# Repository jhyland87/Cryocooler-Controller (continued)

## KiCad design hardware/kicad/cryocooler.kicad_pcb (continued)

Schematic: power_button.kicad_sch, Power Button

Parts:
C24: 100nF; C_0402_1005Metric
C41: 1uF; C_0603_1608Metric
C80: 47nF; C_0603_1608Metric
C84: 470nF; C_0805_2012Metric
D7: STATUS G=on R=standby; LED_Kingbright_APGB0607
D17: BZT52C15; D_SOD-123
Q1: AONR21307; AOS_DFN3x3A_8L_EP1
Q41: BSS138; SOT-23
R7, R8, R20: 10k; R_0402_1005Metric
R27: 100k; R_0402_1005Metric
R56: 220k; R_0402_1005Metric
R59: 82k; R_0402_1005Metric
R93: 13k; R_0402_1005Metric
R401: 2.2k; R_0402_1005Metric
SW3: POWER; SW_TE_1571300-2
U11: LTC2954CDDB-2; DFN-8-1EP_2x3mm_P0.5mm_EP0.61x2.2mm
U12: LM4040DBZ-5; SOT-23
U34: TPD1E05U06DPYR; Texas_DPY0002A_0.6x1mm_P0.65mm

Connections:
+3V3: Q41.1 (G), R8.2; also elsewhere on the board
+5V: R401.1; also elsewhere on the board
/Power Button/PWR_BTN: SW3.1, U11.3 (PB), U34.1 (IO)
/Power Button/STATUS_GA: D7.1 (GA), R401.2
/Power Button/STATUS_RA: D7.4 (RA), Q41.3 (D), R93.2
GND: C24.2, C41.2, D7.2 (GK), D7.3 (RK), Q41.2 (S), SW3.2, U11.1 (GND), U11.9 (EP), U12.2 (A), U34.2 (GND); also elsewhere on the board
unnamed: C80.1, C84.2, D17.2 (A), Q1.4 (G), R20.2, R27.2
unnamed: C41.1, U11.6 (PDT)
unnamed: R20.1, U11.7 (~EN)
unnamed: R7.1, R56.2, U11.5 (~KILL)
unnamed: R56.1, R59.2, U12.1 (K)
PWR_INT: R8.1, U11.8 (~INT); also elsewhere on the board
PWR_KILL: R7.2; also elsewhere on the board
VIN: C24.1, C84.1, D17.1 (K), Q1.1 (S), Q1.2 (S), Q1.3 (S), R27.1, R59.1, R93.1, U11.4 (VIN); also elsewhere on the board
VSW: C80.2, Q1.5 (D), Q1.6 (D), Q1.7 (D), Q1.8 (D); also elsewhere on the board

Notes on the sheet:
Q1 gate: 10k series and 47 nF to the drain limit the ramp to about 20 V/ms; 470 nF to the source holds Vgs under 1.1 V on a hot plug (10 x Cgd); the Zener caps Vgs at 15 V for input transients up to the 26 V TVS clamp.
STATUS LED: red = standby (about 0.8 mA from VIN, off when +3V3 is up), green = on (+5V, about 1 mA), both = +3V3 missing
LTC2954 DECOUPLING CAPACITORS
LTC2954-2: tap PB = on, hold = off. EN# drives the P-FET gate; KILL# from GPIO10 (active low, 100 ms pulse). INT# tells GPIO1 to shut down cleanly; holding PB cuts power about 6.4 s later (1 uF on PDT).

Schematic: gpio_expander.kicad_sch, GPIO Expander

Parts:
C35: 100nF; C_0402_1005Metric
U25: MCP23S08-E/ML; QFN-20-1EP_4x4mm_P0.5mm_EP2.7x2.7mm

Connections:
+3V3: C35.1, U25.4 (~RESET), U25.18 (VDD); also elsewhere on the board
DISP_BL_EN: U25.13 (GP4); also elsewhere on the board
EXPANDER_CS: U25.5 (~CS); also elsewhere on the board
GND: C35.2, U25.2 (A1), U25.3 (A0), U25.17 (VSS), U25.21 (EP); also elsewhere on the board
INA239_ALERT: U25.15 (GP6); also elsewhere on the board
PGN_15V: U25.10 (GP1); also elsewhere on the board
PGP_15V: U25.9 (GP0); also elsewhere on the board
SPI_MISO: U25.1 (SO); also elsewhere on the board
SPI_MOSI: U25.20 (SI); also elsewhere on the board
SPI_SCK: U25.19 (SCK); also elsewhere on the board
TOUCH_IRQ: U25.16 (GP7); also elsewhere on the board

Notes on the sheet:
All pins power up as inputs. RESET, A1 and A0 must be biased (datasheet Table 1-1). Exposed pad to VSS, in addition to pin 17. GP2, GP3 and GP5 are spare; firmware enables weak pull-ups on them. TSC2046 PENIRQ drives GP7.
MCP23S08 DECOUPLING CAPACITOR
MCP23S08: SPI mode 0 slave on the main bus (CS from the decoder). SO releases within 100 ns of CS rising (datasheet Fig. 2-6, parameter 14), so it shares SPI_MISO without a buffer. A1/A0 low: opcodes 0x40 / 0x41.

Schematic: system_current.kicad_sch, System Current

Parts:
C32: 100nF; C_0402_1005Metric
C46: 1uF; C_0603_1608Metric
C66: 100uF/25V; CP_Elec_8x10
C68: 100nF; C_0805_2012Metric
C83: 470nF; C_0805_2012Metric
D6: ALERT (red); LED_Kingbright_APGB0607
R9: 10k; R_0402_1005Metric
R78: 15m; R_2512_6332Metric
R79, R80: 49.9; R_0402_1005Metric
R81: 1.5k; R_0402_1005Metric
U23: INA239AIDGSR; TSSOP-10_3x3mm_P0.5mm

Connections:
+3V3: C32.1, C46.1, R9.2, R81.1, U23.6 (VS); also elsewhere on the board
+12V: C66.1, C68.1, R78.2, R79.1; also elsewhere on the board
/System Current/ALERT_LED_A: D6.4 (RA), R81.2
GND: C32.2, C46.2, C66.2, C68.2, U23.7 (GND); also elsewhere on the board
INA239_ALERT: D6.3 (RK), R9.1, U23.3 (~ALERT); also elsewhere on the board
INA239_CS: U23.1 (~CS); also elsewhere on the board
unnamed: C83.2, R80.2, U23.10 (IN+)
unnamed: C83.1, R79.2, U23.8 (VBUS), U23.9 (IN-)
SPI_MISO: U23.4 (SDO); also elsewhere on the board
SPI_MOSI: U23.2 (SDI); also elsewhere on the board
SPI_SCK: U23.5 (SCLK); also elsewhere on the board
VSW: R78.1, R80.1; also elsewhere on the board

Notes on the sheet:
INA239 DECOUPLING CAPACITORS
INA239 monitors the switched 12 V rail: 15 mOhm shunt, SPI mode 1 on the main bus (CS from the decoder), +/-163.84 mV range (~10.9 A). ALERT drives its LED and MCP23S08 GP6.

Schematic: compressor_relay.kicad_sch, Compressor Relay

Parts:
D3: COMP_RELAY G=on R=off; LED_Kingbright_APGB0607
D14: 1N4148W; D_SOD-123
J13: COMPRESSOR RELAY / GND; XKB_X2510WRS-02-9TSN_1x02_P2.54mm_Horizontal
Q7: BSS138; SOT-23
Q8: BSS84; SOT-23
R30, R31: 100k; R_0402_1005Metric
R45: 4.7k; R_0402_1005Metric
R51: 1k; R_0402_1005Metric
R61: 2.2k; R_0402_1005Metric

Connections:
+5V: R61.1; also elsewhere on the board
+12V: Q8.2 (S), R31.1; also elsewhere on the board
/Compressor Relay/COMP_RELAY: D3.1 (GA), D3.3 (RK), D14.1 (K), J13.1, Q8.3 (D), R45.1
/Compressor Relay/COMP_RELAY_LED: D3.2 (GK), D3.4 (RA), R61.2
COMP_RELAY_EN: R51.1; also elsewhere on the board
GND: D14.2 (A), J13.2, Q7.2 (S), R30.2, R45.2; also elsewhere on the board
unnamed: Q7.3 (D), Q8.1 (G), R31.2
unnamed: Q7.1 (G), R30.1, R51.2

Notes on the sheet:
COMP_RELAY_EN (GPIO16) high -> +12 V on the compressor relay terminal (BSS84 high-side switch, 130 mA max: drive an external relay or SSR coil). Flyback diode across the output. LED: green = on, red = off.

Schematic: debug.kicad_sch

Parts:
D10: ISO 5V (green); LED_Kingbright_APGB0607
R38: 3.3k; R_0402_1005Metric
TP9: +15V; TestPoint_Pad_D1.0mm
TP10: -15V; TestPoint_Pad_D1.0mm
TP11: +16V5; TestPoint_Pad_D1.0mm
TP12: -16V5; TestPoint_Pad_D1.0mm
TP14: GND; TestPoint_Keystone_5015_Micro_Mini
TP37: DDS; TestPoint_Pad_D1.0mm
TP38: SINE; TestPoint_Pad_D1.0mm

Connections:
+15V: TP9.1; also elsewhere on the board
+16V5: TP11.1; also elsewhere on the board
-15V: TP10.1; also elsewhere on the board
-16V5: TP12.1; also elsewhere on the board
/Debug/ISO_5V_LED_A: D10.1 (GA), R38.2
DDS_SINE: TP37.1; also elsewhere on the board
GND: TP14.1; also elsewhere on the board
ISO_5V: R38.1; also elsewhere on the board
ISO_GND: D10.2 (GK); also elsewhere on the board
SIG_SINE: TP38.1; also elsewhere on the board

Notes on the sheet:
GROUND (scope loops)
RAIL LEDS
FAN, PUMP, INTERRUPTS AND CONTROL
ANALOG AND SENSORS
POWER RAILS
Debug aids: test points (pad per net, loops for ground) and rail LEDs. Each test point sits on a global label or power symbol; the PCB generator places it beside a pad on the same net.

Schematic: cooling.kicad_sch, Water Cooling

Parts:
C23: 100nF; C_0402_1005Metric
C76, C77: 22uF/25V; C_1210_3225Metric
J3: FAN (4-pin PWM); XKB_X2510WRS-04-9TSN_1x04_P2.54mm_Horizontal
J4: PUMP (4-pin PWM); XKB_X2510WRS-04-9TSN_1x04_P2.54mm_Horizontal
J5: ALPHACOOL ES FLOW (pin 4 NC); XKB_X2510WRS-04-9TSN_1x04_P2.54mm_Horizontal
J6: ALPHACOOL ES NTC 10k; XKB_X2510WRS-02-9TSN_1x02_P2.54mm_Horizontal
Q61: BSS138DW; SOT-363_SC-70-6
R6, R15, R16: 10k; R_0402_1005Metric
R43: 4.7k; R_0402_1005Metric
R53, R54: 1k; R_0402_1005Metric
RN1: 4.7k; R_Array_Convex_4x0402
RN2: 10k; R_Array_Convex_4x0402
U33: SP3422-04UTG; Littelfuse_DFN-5_1.0x0.6mm_P0.35mm

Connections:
+3V3: R15.1, R16.1; also elsewhere on the board
+3V3_COOL: R6.1, RN1.6 (R3.2), RN1.8 (R1.2), RN2.4 (R4.1), RN2.5 (R4.2), RN2.6 (R3.2), RN2.7 (R2.2), RN2.8 (R1.2); also elsewhere on the board
+12V: C76.1, C77.1, J3.2, J4.2, J5.2; also elsewhere on the board
FAN_PWM: R15.2, R53.1; also elsewhere on the board
FAN_TACH: RN1.7 (R2.2), U33.1 (IO1); also elsewhere on the board
FLOW_TACH: R43.1, RN2.3 (R3.1), U33.4 (IO3); also elsewhere on the board
GND: C23.2, C76.2, C77.2, J3.1, J4.1, J5.1, J6.2, Q61.1 (S), Q61.4 (S), U33.2 (GND); also elsewhere on the board
NTC_ADC: C23.1, J6.1, R6.2, U33.5 (IO4); also elsewhere on the board
unnamed: J3.3, RN1.1 (R1.1), RN1.2 (R2.1)
unnamed: J3.4, Q61.6 (D), RN2.1 (R1.1)
unnamed: J4.3, RN1.3 (R3.1), RN1.4 (R4.1)
unnamed: J4.4, Q61.3 (D), RN2.2 (R2.1)
unnamed: J5.3, R43.2
unnamed: Q61.2 (G), R53.2
unnamed: Q61.5 (G), R54.2
PUMP_PWM: R16.2, R54.1; also elsewhere on the board
PUMP_TACH: RN1.5 (R4.2), U33.3 (IO2); also elsewhere on the board

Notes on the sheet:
SPARE 10k ELEMENT
Tach: open collector, 2 pulses/rev, counted with PCNT. Alphacool ES: tach -> GPIO18, NTC -> GPIO4.
Fan and pump: LEDC PWM at 25 kHz through one BSS138DW element each, because the PWM input can sit at 5.25 V (Intel 4-wire spec) and GPIOs are not 5 V tolerant. GPIO high = FET on = 0% drive; firmware inverts the duty.
ESD CLAMP (GPIO SIDE)

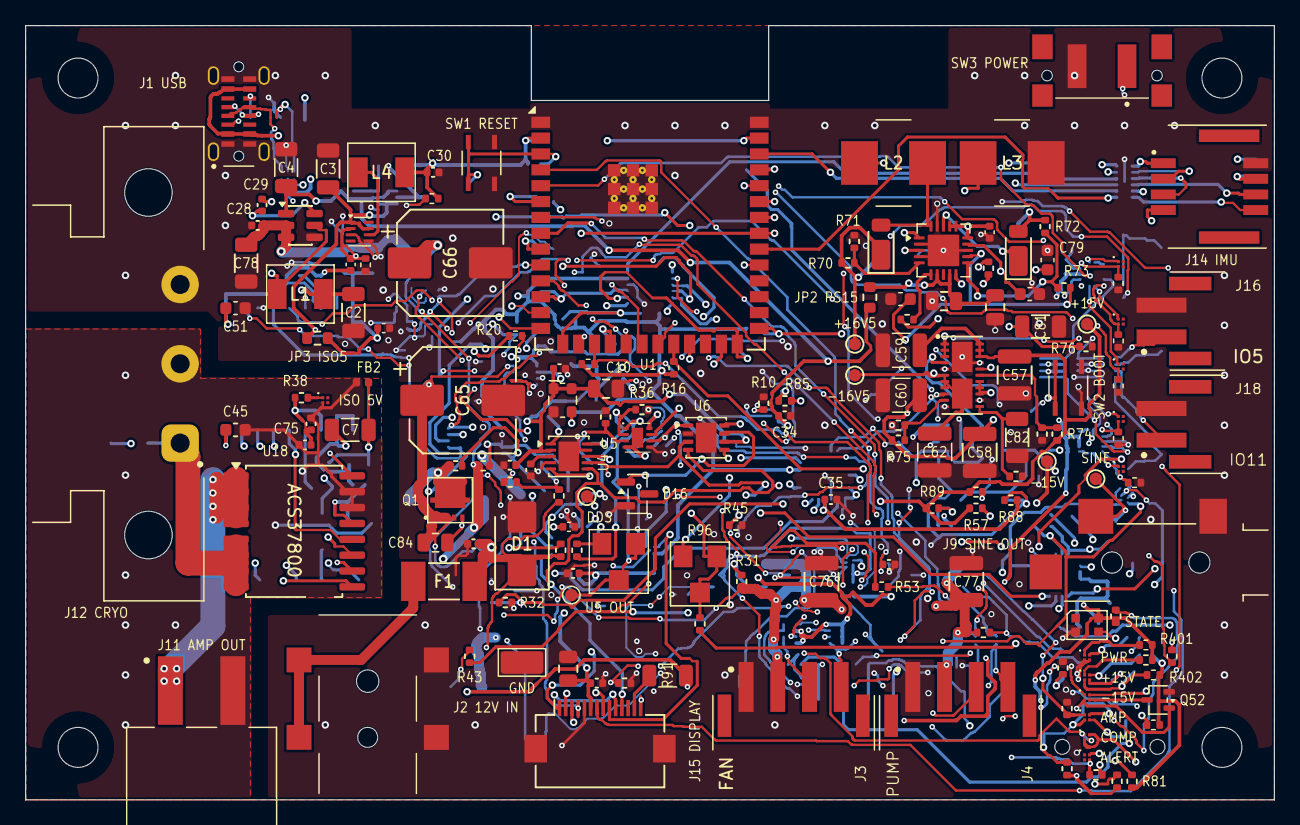
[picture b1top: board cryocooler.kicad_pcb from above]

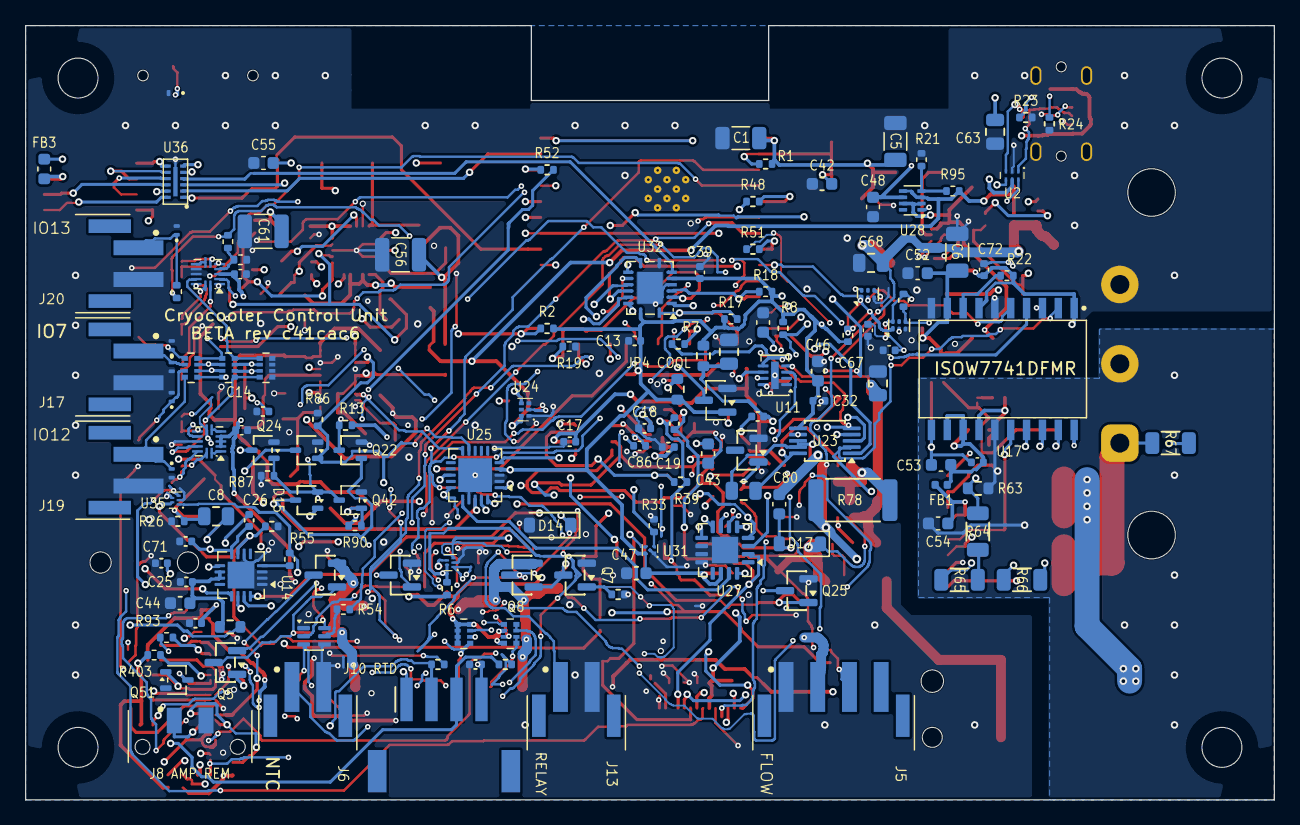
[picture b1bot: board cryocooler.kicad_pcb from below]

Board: 4 copper layers, 100.0 x 62.0 mm, 309 parts (146 on the bottom side), 204 nets.

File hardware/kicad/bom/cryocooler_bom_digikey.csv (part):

Quantity,Manufacturer Part Number,Manufacturer,Description,Customer Reference,Value,Package,MPN basis,Notes
7,CL31A226KPHNNNE,Samsung Electro-Mechanics,CAP CER 22UF 10V X5R 1206,C1-C7,22uF/10V,C_1206_3216Metric,suggested,"5 V and 3.3 V buck outputs, ISOW7741 VDD and VISOOUT, ESP32"
5,CL21A106KACLRNC,Samsung Electro-Mechanics,CAP CER 10UF 25V X5R 0805,C8-C12,10uF,C_0805_2012Metric,ordered,substitute for CL21A106KAYNNNE
30,CL05B104KB54PNC,Samsung Electro-Mechanics,CAP CER 0.1UF 50V X7R 0402,C13-C20 C23-C40 C301-C304,100nF,C_0402_1005Metric,suggested,
14,CL10A105KB8NNNC,Samsung Electro-Mechanics,CAP CER 1UF 50V X5R 0603,C41-C54,1uF,C_0603_1608Metric,suggested,
1,CL10B683KB8NNNC,Samsung Electro-Mechanics,CAP CER 0.068UF 50V X7R 0603,C55,68nF,C_0603_1608Metric,suggested,ADP5071 COMP2
7,GRM32ER71E226KE15L,Murata,CAP CER 22UF 25V X7R 1210,C56-C62,22uF/25V X7R,C_1210_3225Metric,suggested,"ADP5071 outputs / LT3097 inputs and LT3097 outputs; the LT3097 needs >= 10 uF effective at 15 V DC bias (INN and both outputs have two in parallel; INP needs 4.7 uF), so check the DC-bias curve"
2,C2012X5R1E475K085AC,TDK,CAP CER 4.7UF 25V X5R 0805,C63 C64,4.7uF,C_0805_2012Metric,ordered,USB VBUS filter; substitute for CL21A475KAQNNNE
1,EEE-FK1V101P,Panasonic,CAP ALUM 100UF 20% 35V SMD 8x10.2,C65,100uF/35V,CP_Elec_8x10,suggested,"C65 sits on the input rail behind a 26 V TVS clamp; rating taken from distributor listings, not a Panasonic datasheet"
1,EEE-FK1E101AP,Panasonic,CAP ALUM 100UF 20% 25V SMD 8x10.2,C66,100uF/25V,CP_Elec_8x10,ordered,switched +12 V rail; substitute for EEE-FK1E101P
2,CL21B104KBCNNNC,Samsung Electro-Mechanics,CAP CER 0.1UF 50V X7R 0805,C67 C68,100nF,C_0805_2012Metric,suggested,
7,CL05B103KB5NNNC,Samsung Electro-Mechanics,CAP CER 10000PF 50V X7R 0402,C69-C75,10nF,C_0402_1005Metric,suggested,
2,C1210C226K3PACTU,Kemet,CAP CER 22UF 25V X5R 1210,C76 C77,22uF/25V,C_1210_3225Metric,ordered,12 V rail; substitute for CL32A226KAJNNNE
1,CL31A106KBHNNNE,Samsung Electro-Mechanics,CAP CER 10UF 50V X5R 1206,C78,10uF/50V,C_1206_3216Metric,suggested,12 V rail (U15 input); 50 V so it is rated over the SMBJ16A clamp (about 26 V); JLCPCB C13585 (basic)
2,CL10B473KB8NNNC,Samsung Electro-Mechanics,CAP CER 0.047UF 50V X7R 0603,C79 C80,47nF,C_0603_1608Metric,suggested,ADP5071 COMP1; Q1 gate-drain slow start
2,CL31B105KBHNNNE,Samsung Electro-Mechanics,CAP CER 1UF 50V X7R 1206,C81 C82,1uF/50V,C_1206_3216Metric,suggested,LT3097 SETP / SETN bypass (the pins sit at 14.7 V DC)
2,CL21B474KBFNNNE,Samsung Electro-Mechanics,CAP CER 0.47UF 50V X7R 0805,C83 C84,470nF,C_0805_2012Metric,suggested,INA239 input filter across IN+/IN-; Q1 gate-source
1,CL05C102JB5NNNC,Samsung Electro-Mechanics,CAP CER 1000PF 50V C0G 0402,C85,1nF/C0G,C_0402_1005Metric,suggested,across R35 + R92 (50.6k) in the sine gain stage
1,CL05C220JB5NNNC,Samsung Electro-Mechanics,CAP CER 22PF 50V C0G 0402,C86,22pF/C0G,C_0402_1005Metric,suggested,"AD5453 output stage stability (datasheet C1), sized for the OPA2991"
1,CL05C121JB5NNNC,Samsung Electro-Mechanics,CAP CER 120PF 50V C0G 0402,C87,120pF,C_0402_1005Metric,suggested,TPS62822 feed-forward across the 453k
1,SMBJ16A,Littelfuse,TVS DIODE 16VWM 26VC DO214AA,D1,SMBJ16A,D_SMB,design,unidirectional
12,APGB0607G22R23C,Kingbright,LED GREEN/RED BICOLOR 0.65X0.65MM SMD,D2 D3 D6 D7 D10-D12 D81-D85,APGB0607G22R23C,LED_Kingbright_APGB0607,design,"all indicators but D13; independent dies, about 1 mA each. D6 and D10 use one die"
2,DFLS240-7,Diodes Incorporated,DIODE SCHOTTKY 40V 2A POWERDI123,D4 D5,DFLS240,D_PowerDI-123,design,
1,4684,Adafruit,LED RGB NEOPIXEL NANO WS2812B-2020 2 X 2 MM (10 pack),D13,WS2812B-2020,LED_WS2812B-2020_PLCC4_2.0x2.0mm,design,Adafruit listed the 10 pack out of stock on 2026-11-06; the 100 pack is Adafruit 6428. Check JLCPCB/LCSC for a WS2812B-2020 if you assemble there
1,1N4148W-7-F,Diodes Incorporated,DIODE GEN PURP 75V 150MA SOD123,D14,1N4148W,D_SOD-123,design,
1,BAT54AW-7-F,Diodes Incorporated,DIODE ARR SCHOTTKY 30V 200MA SOT323,D15,BAT54AW,SOT-323_SC-70,design,"common anode on PG_15V (pin 3), cathodes on pins 1 and 2"
1,MMBZ9V1ALT1G,onsemi,TVS DIODE 6VWM DUAL COMMON ANODE SOT23-3,D16,MMBZ9V1ALT1G,SOT-23,design,"AD5453 VREF clamp: used between cathodes, under 10.5 V"
1,BZT52C15-7-F,Diodes Incorporated,DIODE ZENER 15V 500MW SOD123,D17,BZT52C15,D_SOD-123,suggested,"Q1 gate clamp, 13.8-15.6 V"
1,0453005.MR,Littelfuse,FUSE BRD MNT 5A 125VAC/VDC 2SMD,F1,5A backup,Fuse_Littelfuse-NANO2-451_453,suggested,"NANO2 453 series, fast acting, 2410 package (6.1 x 2.7 mm); backup only: add a fuse at the PSU end (see DESIGN_REVIEW.md)"
2,BLM15EX331SN1D,Murata,FERRITE BEAD 330 OHM 100MHZ 0402,FB1 FB2,BLM15EX331SN1D,L_0402_1005Metric,design,"ISOW7741 VISOOUT and GND2 beads, named by the TI datasheet"
1,BLM18PG121SN1D,Murata,FERRITE BEAD 120 OHM 100MHZ 2A 0603,FB3,BLM18PG121SN1D,L_0603_1608Metric,suggested,ahead of JP5 on the cold head supply; rating from distributor listings
1,USB4210-GF-A,GCT,"USB-C 2.0 RECEPTACLE 16P, FLAG TYPE, TOP MOUNT",J1,USB_C,USB_C_Receptacle_GCT_USB4205-GF-A_16P_Flag,design,"J1: stands on its side, 9.89 mm high, mouth 3 mm past the board edge; four plated shell stakes and two pegs. Same land pattern as the 12.5 mm USB4205-GF-A the footprint is named after (GCT drawing USB4210 rev A2)"
1,54-00164,Tensility,CONN JACK R/A SMT 5.5X2.1MM,J2,,Tensility_54-00164_5.5x2.1mm_Horizontal_SMD,design,"J2 12 V in, centre pin positive; 5.5 A up to 40 C, derates to 0 at 70 C; do not mate under load"
3,X2510WRS-04-9TSN,XKB Connectivity,"CONN HEADER R/A SMT 4POS 2.54MM, 4 A",J3-J5,,XKB_X2510WRS-04-9TSN_1x04_P2.54mm_Horizontal,design,"J3 fan, J4 pump, J5 flow sensor (pin 4 unused); mates with X2510H-04 housings, so fan, pump and flow leads are re-housed"
7,X2510WRS-02-9TSN,XKB Connectivity,"CONN HEADER R/A SMT 2POS 2.54MM, 4 A",J6 J13 J16-J20,,XKB_X2510WRS-02-9TSN_1x02_P2.54mm_Horizontal,design,"J6 NTC, J13 relay 12 V out, J16-J20 general-purpose I/O; mates with X2510H-02 housings and X2510T terminals"
1,1821698,Phoenix Contact,"PCB HEADER MC 0,5/ 2-G-2,54 SMD R24, 6 A",J8,,"PhoenixContact_MC_0,5_2-G-2,54_SMD_1x02_P2.54mm_Horizontal",design,"J8 amplifier REM. Mating plug FMC 0,5/ 2-ST-2,54 (confirm the plug item number before ordering)"
1,MJ-3523-SMT-TR,Same Sky,CONN JACK MONO 3.5MM SMD,J9,,SameSky_MJ-3523-SMT-TR_3.5mm_Horizontal_SMD,design,"J9 amplifier signal: tip = signal, sleeve = GND"
1,4392,Adafruit,"CONN HEADER JST PH COMPATIBLE R/A SMT 4POS 2MM, 2 A",J10,,Adafruit_4392_JST-PH_1x04_P2.00mm_Horizontal_SMD,design,J10 PT1000 4-wire (F+ / S+ / S- / F-); Kaweei CW2001-04T-H01-BD-A; mates with a JST PHR-4 housing or JST PH 4-pin pigtail
1,2305908-2,TE Connectivity,"CONN HEADER R/A SMT 2POS 5MM, 15 A",J11,,TE_2305908-2_1x02_P5.00mm_Horizontal_SMD,design,J11 amp out. SMT pads carry all plugging force. Mates with TE 2213934 / 2213935 / 2305909 series plugs (confirm the plug item number before ordering)
1,643228-1,TE Connectivity,"CONN HEADER R/A TH 3POS 6.35MM, UNIVERSAL MATE-N-LOK",J12,,TE_643228-1_1x03_P6.35mm_Horizontal,design,"J12 cryocooler: pin 1 +, pin 2 -, pin 3 GND (the plug's protective ground, tied to board GND). Through hole, soldered by hand or selectively, plus 2 screws through the 3.81 mm ear holes. Listed mating plugs: TE 350766-1, 770018-1; one distributor lists 12 A / 600 V (confirm plug and rating with TE before ordering)"
1,505448-0891,Molex,CONN HEADER R/A 8POS 1.25MM DUAL ROW SMD,J14,505448-0891,Molex_Micro-Lock_Plus_505448-0891_2x04_P1.25mm_Horizontal,design,"J14 IMU cable; Micro-Lock Plus, positive lock, 30 mating cycles; mates with a 505432 series 8-circuit dual-row housing"
1,FH12-14S-0.5SH(55),Hirose,CONN FFC BOTTOM 14POS 0.50MM R/A,J15,FH12-14S-0.5SH(55),Hirose_FH12-14S-0.5SH_1x14-1MP_P0.50mm_Horizontal,design,display FPC (Phoenix datasheet 109921); check the FFC contact side so pin 1 lands on pin 1
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
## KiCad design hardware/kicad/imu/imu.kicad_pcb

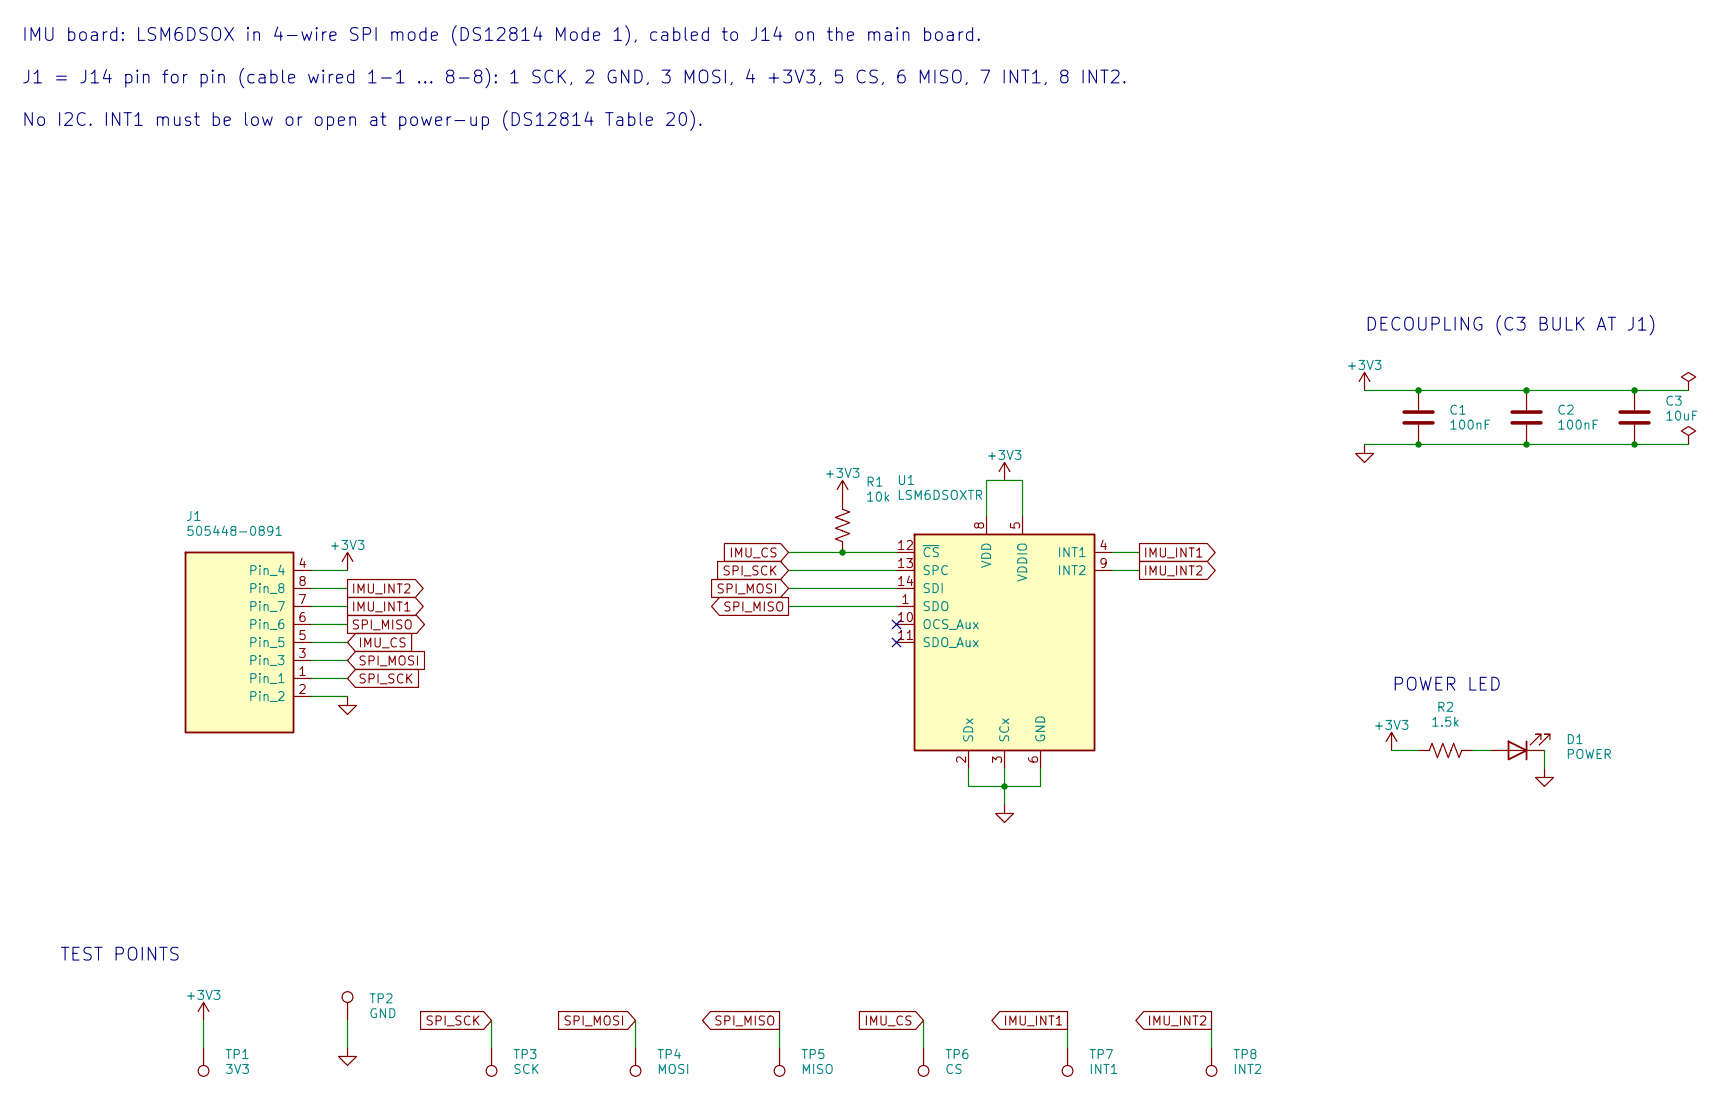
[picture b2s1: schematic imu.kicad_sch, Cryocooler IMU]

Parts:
C1, C2: 100nF; C_0402_1005Metric
C3: 10uF; C_0805_2012Metric
D1: POWER; LED_0402_1005Metric
J1: 505448-0891; Molex_Micro-Lock_Plus_505448-0891_2x04_P1.25mm_Horizontal
R1: 10k; R_0402_1005Metric
R2: 1.5k; R_0402_1005Metric
TP1: 3V3; TestPoint_Pad_D1.0mm
TP2: GND; TestPoint_Pad_D1.0mm
TP3: SCK; TestPoint_Pad_D1.0mm
TP4: MOSI; TestPoint_Pad_D1.0mm
TP5: MISO; TestPoint_Pad_D1.0mm
TP6: CS; TestPoint_Pad_D1.0mm
TP7: INT1; TestPoint_Pad_D1.0mm
TP8: INT2; TestPoint_Pad_D1.0mm
U1: LSM6DSOXTR; LGA-14_3x2.5mm_P0.5mm_LayoutBorder3x4y

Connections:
+3V3: C1.1, C2.1, C3.1, J1.4, R1.1, R2.1, TP1.1, U1.5 (VDDIO), U1.8 (VDD)
GND: C1.2, C2.2, C3.2, D1.1 (K), J1.2, TP2.1, U1.2 (SDx), U1.3 (SCx), U1.6 (GND), U1.7 (GND)
IMU_CS: J1.5, R1.2, TP6.1, U1.12 (~CS)
IMU_INT1: J1.7, TP7.1, U1.4 (INT1)
IMU_INT2: J1.8, TP8.1, U1.9 (INT2)
unnamed: D1.2 (A), R2.2
SPI_MISO: J1.6, TP5.1, U1.1 (SDO)
SPI_MOSI: J1.3, TP4.1, U1.14 (SDI)
SPI_SCK: J1.1, TP3.1, U1.13 (SPC)

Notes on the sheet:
DECOUPLING (C3 BULK AT J1)
No I2C. INT1 must be low or open at power-up (DS12814 Table 20).
TEST POINTS
J1 = J14 pin for pin (cable wired 1-1 ... 8-8): 1 SCK, 2 GND, 3 MOSI, 4 +3V3, 5 CS, 6 MISO, 7 INT1, 8 INT2.
POWER LED
IMU board: LSM6DSOX in 4-wire SPI mode (DS12814 Mode 1), cabled to J14 on the main board.

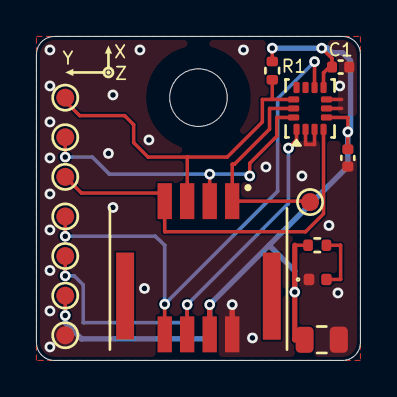
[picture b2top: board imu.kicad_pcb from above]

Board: 2 copper layers, 18.0 x 18.0 mm, 16 parts (0 on the bottom side), 9 nets.

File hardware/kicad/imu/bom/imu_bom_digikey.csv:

Quantity,Manufacturer Part Number,Manufacturer,Description,Customer Reference,Value,Package,MPN basis,Notes
2,CL05B104KB54PNC,Samsung Electro-Mechanics,CAP CER 0.1UF 50V X7R 0402,C1 C2,100nF,C_0402_1005Metric,suggested,
1,CL21A106KACLRNC,Samsung Electro-Mechanics,CAP CER 10UF 25V X5R 0805,C3,10uF,C_0805_2012Metric,ordered,substitute for CL21A106KAYNNNE
1,APHHS1005CGCK,Kingbright,LED GREEN (570 NM) CLEAR 0402 SMD,D1,green,LED_0402_1005Metric,suggested,"indicators sized for ~1 mA (1.5k on 3.3 V, 3.3k on 5 V, 13k on 15 V); AlGaInP green, Vf 2.1 V typ"
1,505448-0891,Molex,CONN HEADER R/A 8POS 1.25MM DUAL ROW SMD,J1,505448-0891,Molex_Micro-Lock_Plus_505448-0891_2x04_P1.25mm_Horizontal,design,"J14 IMU cable; Micro-Lock Plus, positive lock, 30 mating cycles; mates with a 505432 series 8-circuit dual-row housing"
1,RC0402FR-0710KL,Yageo,RES 10K OHM 1% 1/16W 0402,R1,10k,R_0402_1005Metric,suggested,
1,RC0402FR-071K5L,Yageo,RES 1.5K OHM 1% 1/16W 0402,R2,1.5k,R_0402_1005Metric,suggested,
1,LSM6DSOXTR,STMicroelectronics,IMU ACCEL/GYRO I2C/SPI 14LGA,U1,LSM6DSOXTR,LGA-14_3x2.5mm_P0.5mm_LayoutBorder3x4y,design,"IMU board (imu/): SPI mode, datasheet DS12814"

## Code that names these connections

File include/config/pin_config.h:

/**
 * @file pin_config.h
 * @brief Pin assignments for ESP32-S3 peripherals
 *
 * Central location for all GPIO and SPI pin definitions.
 * Update this file when changing wiring or board layout.
 *
 * Relay and indicator pins marked TODO must be wired to the actual
 * hardware and assigned before deployment.
 */

#ifndef PIN_CONFIG_H
#define PIN_CONFIG_H


#define RGB_LED_PIN 38

// =============================================================================
// Shared SPI bus chip selects: SN74LVC138A decoder (U32)
// =============================================================================
// A/B/C pick the output and G2A enables it (10 kOhm pull-up holds it off at boot).
// GPIO3 and GPIO45 are strapping pins: 10 kOhm resistors hold GPIO3 high (default
// USB-JTAG) and GPIO45 low at reset. GPIO44 is U0RXD; the console is native USB
// CDC, so UART0 is unused. GPIO47 (1.8 V only) is free.
#define CS_ADDR_A_PIN      3
#define CS_ADDR_B_PIN      44
#define CS_ADDR_C_PIN      45
#define CS_ENABLE_PIN      8

// *_CS values below are not GPIOs: src/spi_select.cpp catches these IDs in
// pinMode() and digitalWrite() and drives the decoder. ID - CS_ID_BASE is the
// output number. They must stay above RGB_BUILTIN (97) and fit an int8_t, which
// is how Adafruit BusIO stores CS.
#define CS_ID_BASE         100
#define CS_OUTPUT_COUNT    8

// MCP23S08 SPI GPIO expander — SPI mode 0 on the shared SPI bus. See the
// EXPANDER_PIN_* map below. RESET is tied high; INT is not wired to the MCU.
#define EXPANDER_CS_PIN    (CS_ID_BASE + 3)

// AD5453 14-bit multiplying DAC — amplitude control. SPI mode 1, writes only.
#define AD5453_SYNC        (CS_ID_BASE + 1)

// INA239 power monitor — SPI mode 1 on the shared SPI bus (MISO is Hi-Z when CS is high).
#define INA239_CS          (CS_ID_BASE + 2)

// ADS1220 RTD ADC — SPI mode 1 on the shared SPI bus (DOUT is Hi-Z when CS is high).
// DRDY is not wired to the MCU.
#define ADS1220_CS         (CS_ID_BASE + 6)

// LSM6DSOX IMU — Adafruit breakout (product 4438) mounted on the cryocooler and
// cabled to header J14; SPI on the shared bus (AD9833, AD5453, ...).
#define LSM6DSOX_CS        (CS_ID_BASE + 7)    // J14 pin 5
#define LSM6DSOX_INT1_PIN  2    // J14 pin 7
#define LSM6DSOX_INT2_PIN  39   // J14 pin 8

// =============================================================================
// AD9833 Waveform Generator
// =============================================================================
#define AD9833_CS          (CS_ID_BASE + 0)    // Chip Select for AD9833

// Compressor relay driver (active HIGH): BSS138 + BSS84 high-side switch puts
// +12 V on the compressor relay terminal (130 mA max).
#define COMPRESSOR_RELAY_PIN 16

// LTC2954 power button handshake. INT# pulses low (32 ms minimum, 10 kOhm
// pull-up R8) when the button asks for power-off; driving KILL# low releases
// the supply. The LTC2954 cuts power by itself if the button is held 6.4 s.
#define PWR_INT_PIN       1
#define PWR_KILL_PIN      10

// =============================================================================
// SPI Bus (AD9833, AD5453, LSM6DSOX, INA239, ADS1220, MCP23S08, ST7789V, TSC2046,
// ACS37800)
// =============================================================================
// Why am I not using values from /Users/justinhyland/.platformio/packages/framework-arduinoespressif32/variants/esp32s3/pins_arduino.h?
// or /Users/justinhyland/.platformio/packages/framework-arduinoespressif32/variants/esp32_s3r8n16/pins_arduino.h
#define SPI_MISO          40    // Master In Slave Out  (read by the LSM6DSOX, INA239, ADS1220 and ACS37800)
#define SPI_MOSI          41    // Master Out Slave In  (AD5453 SDIN + AD9833 SDATA + LSM6DSOX SDI + INA239 MOSI)
#define SPI_CLK           42    // SPI Clock


// ACS37800 power monitor (U18, behind the U17 ISOW7741 isolator): SPI mode 3, LSB
// first, on the shared SPI bus. It keeps driving MISO while CS is high, so two
// SN74LVC1G125 gates with /OE on ACS_CS connect it only while CS is low: one passes
// SCK to the isolator, the other its MISO to the bus. A 10 kOhm pull-up holds CS
// high while the GPIO floats. CS is a plain GPIO, not a decoder ID.
// CS is GPIO17, not GPIO43: GPIO43 is U0TXD and toggles with ROM boot messages at reset.
#define ACS37800_CS        17

// =============================================================================
// General-purpose I/O headers (IO5, IO7, IO11, IO12, IO13)
// =============================================================================
// Each pin has a 100 Ohm series resistor, 200 kOhm to ground, an ESD clamp and an
// indicator LED whose brightness follows the pin voltage. Only GPIO5 and GPIO7 are
// ADC1 and can read analog with WiFi on; GPIO11 to GPIO13 are ADC2.
#define AUX_IO5_PIN        5
#define AUX_IO7_PIN        7
#define AUX_IO11_PIN       11
#define AUX_IO12_PIN       12
#define AUX_IO13_PIN       13

// =============================================================================
// Alphacool ES High Flow + Temperature Sensor
// =============================================================================

// Hall-effect flow pulse input (open-drain, active LOW).
// Requires a 10 kΩ pull-up to 3.3 V on the line; the internal INPUT_PULLUP
// is used as a backup but an external resistor is strongly recommended.
#define COOLING_FLOW_PIN         18

// Fan and pump 4-pin PWM outputs, each through a BSS138: GPIO high pulls the
// PWM line low (0 % drive).  The line can sit at up to 5.25 V, so it must not
// connect to a GPIO directly.  A 10 kΩ gate pull-up holds 0 % drive during boot.
#define COOLING_FAN_PWM_PIN      9
#define COOLING_PUMP_PWM_PIN     14

// Fan and pump tach inputs (open collector, 2 pulses per revolution), pulled up
// to 3.3 V at the connector, with a 4.7 kΩ series resistor and a clamp to the GPIO.
#define COOLING_FAN_TACH_PIN     15
#define COOLING_PUMP_TACH_PIN    21

// ADC input for the NTC coolant temperature sensor.
// Wiring: 3.3 V → 10 kΩ (ref) → GPIO → NTC sensor → GND
// Use ADC1 channels only (GPIO 1–10 on ESP32-S3) to avoid ADC2 Wi-Fi conflicts.
#define COOLING_TEMP_ADC_PIN     4    // GPIO4 = ADC1-3

// =============================================================================
// On-board WS2812 RGB Status LED
// =============================================================================
#define STATUS_LED_PIN     RGB_LED_PIN   // Common for on-board RGB on ESP32-S3 DevKit


// =============================================================================
// Amplifier Relay — GPIO-driven (active HIGH closes relay)
// =============================================================================
#define AMPLIFIER_RELAY_PIN          6

// =============================================================================
// +-15 V power good (active LOW)
// =============================================================================
// Low when both LT3097 outputs are in regulation. The hardware already blocks
// AMP_REM while it is high; read it before starting the signal generator.
// GPIO43 is U0TXD (it toggles with ROM boot messages), behind a 1 kOhm series
// resistor; the console is native USB CDC, so UART0 is otherwise unused.
#define PG_15V_N_PIN                 43

// =============================================================================
// Display (Phoenix 2.4" touch display in the UCS 125-87 lid: ST7789V, 4-wire
// SPI half duplex on the shared bus) and its TSC2046 touch controller
// =============================================================================
// GPIO46 is a strapping pin; a 10 kOhm pull-down holds its default (low) level at
// reset, so the display stays in reset until the firmware releases it.
#define DISP_CS_PIN                  (CS_ID_BASE + 4)
#define DISP_DC_PIN                  48
#define DISP_RST_PIN                 46
#define TOUCH_CS_PIN                 (CS_ID_BASE + 5)

// =============================================================================
// MCP23S08 expander pins (read / written over SPI, see gpio_expander.h)
// =============================================================================
#define EXPANDER_PIN_PGP_15V         0   // input: LT3097 +15 V power good
#define EXPANDER_PIN_PGN_15V         1   // input: LT3097 -15 V power good
#define EXPANDER_PIN_SPARE_2         2   // input with weak pull-up, not wired
#define EXPANDER_PIN_SPARE_3         3   // input with weak pull-up, not wired
#define EXPANDER_PIN_DISP_BL         4   // output: display backlight enable
#define EXPANDER_PIN_SPARE_5         5   // input with weak pull-up, not wired
#define EXPANDER_PIN_INA239_ALERT    6   // input: INA239 ALERT (active LOW, R9 pull-up)
#define EXPANDER_PIN_TOUCH_IRQ       7   // input: TSC2046 PENIRQ (active LOW, internal pull-up)

// =============================================================================




#endif // PIN_CONFIG_H

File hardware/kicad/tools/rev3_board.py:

"""Brings the routed UCS 145-125 board to the rev 3 schematic: removes retired parts, swaps
changed footprints, places new parts, syncs pad nets, renames nets whose copper still
fits, and rips copper on nets that changed. Close the open ends with `gen_pcb.py link`,
`gridroute.py` on the DRC report, then the later rev 3 steps in hardware/HANDOFF_rev3.md.

Parts use the reference numbers from before the rev 3 renumber, so run this before
`renumber_refs.py board`. It was run once on the rev 2 board; the placement tables are
kept as the record of what moved.

Usage: rev3_board.py in.kicad_pcb out.kicad_pcb
"""
import json
import math
import sys
from pathlib import Path

import pcbnew

import pcbnetlist
from spi_expander_board import KEEP, add_part, clear_copper_under, net_of, place

MM = pcbnew.FromMM

# Nets whose copper still fits one new net.
RENAMES = {
    'Net-(J10-Pin_1)': 'RTD_1',
    'Net-(J10-Pin_2)': 'RTD_2',
    'Net-(J10-Pin_3)': 'RTD_3',
    'Net-(J10-Pin_4)': 'RTD_4',
    'ISO_3V3': 'ISO_5V',
    'Net-(D7-K)': 'INA239_ALERT',
    'Net-(U11-~{INT})': 'PWR_INT',
    'MCP4921_CS': 'AD5453_SYNC',
    'Net-(Q1-G)': 'Net-(U11-~{EN})',
}
CLEARANCE = 0.16
PLACEMENT_FILE = Path(__file__).with_name('rev3_placement.json')


def load_placement():
    """Returns ref -> [x, y, rotation, bottom], ripped boxes and removed zones."""
    return json.loads(PLACEMENT_FILE.read_text())


def ends(item):
    if item.Type() == pcbnew.PCB_VIA_T:
        return [item.GetPosition()]
    return [item.GetStart(), item.GetEnd()]


def inside(point, box):
    return box[0] <= point.x / 1e6 <= box[2] and box[1] <= point.y / 1e6 <= box[3]


def drop(board, item):
    KEEP.append(item)
    board.Remove(item)


def remove_retired(board, parts):
    for footprint in list(board.GetFootprints()):
        ref = footprint.GetReference()
        if ref and ref not in parts:
            drop(board, footprint)


def swap_footprints(board, parts, spots):
    """Replaces every part whose footprint changed; keeps its spot unless spots says."""
    swapped = {}
    for footprint in list(board.GetFootprints()):
        ref = footprint.GetReference()
        if not ref or ref not in parts:
            continue
        name = parts[ref]['footprint'].split(':')[-1]
        if str(footprint.GetFPID().GetLibItemName()) == name:
            continue
        spot = spots.get(ref, [
            footprint.GetX() / 1e6, footprint.GetY() / 1e6,
            footprint.GetOrientationDegrees(), footprint.IsFlipped()])
        drop(board, footprint)
        swapped[ref] = add_part(board, ref, parts[ref], spot)
    return swapped


def rip(board, spec):
    """Removes copper: spec is [box, nets]; nets '*' means every net but GND."""
    box, nets = spec
    for item in list(board.GetTracks()):
        name = item.GetNetname()
        wanted = (name not in ('GND', 'ISO_GND')) if nets == '*' else name in nets
        if wanted and any(inside(point, box) for point in ends(item)):
            drop(board, item)


def segment_gap(point, start, end):
    """Distance in nm from a point to a segment."""
    delta_x, delta_y = end[0] - start[0], end[1] - start[1]
    length = delta_x * delta_x + delta_y * delta_y
    ratio = 0 if not length else max(0, min(1, (
        (point[0] - start[0]) * delta_x + (point[1] - start[1]) * delta_y) / length))
    return math.hypot(point[0] - start[0] - ratio * delta_x, point[1] - start[1] - ratio * delta_y)


def clear_along(board, net, layer, width, start, end):
    """Rips other nets' copper within clearance of a new track."""
    margin = width / 2 + MM(CLEARANCE)
    steps = max(1, int(math.dist(start, end) / MM(0.05)))
    samples = [(start[0] + (end[0] - start[0]) * step / steps,
                start[1] + (end[1] - start[1]) * step / steps) for step in range(steps + 1)]
    for item in list(board.GetTracks()):
        if item.GetNetname() == net:
            continue
        if item.Type() == pcbnew.PCB_VIA_T:
            where = item.GetPosition()
            reach = margin + item.GetWidth(pcbnew.F_Cu) / 2
            hit = any(math.dist(sample, (where.x, where.y)) < reach for sample in samples)
        else:
            if item.GetLayer() != layer:
                continue
            first, second = item.GetStart(), item.GetEnd()
            reach = margin + item.GetWidth() / 2
            hit = any(segment_gap(sample, (first.x, first.y), (second.x, second.y)) < reach
                      for sample in samples)
        if hit:
            drop(board, item)


def add_copper(board, plan):
    """Draws the hand-placed power copper, clearing whatever crosses it."""
    for net, layer_name, width, points in plan['tracks']:
        layer = board.GetLayerID(layer_name)
        for first, second in zip(points, points[1:]):
            start = (MM(first[0]), MM(first[1]))
            end = (MM(second[0]), MM(second[1]))
            clear_along(board, net, layer, MM(width), start, end)
            track = pcbnew.PCB_TRACK(board)
            track.SetStart(pcbnew.VECTOR2I(*start))
            track.SetEnd(pcbnew.VECTOR2I(*end))
            track.SetLayer(layer)
            track.SetWidth(MM(width))
            track.SetNet(net_of(board, net))
            board.Add(track)
            KEEP.append(track)
    for net, pos_x, pos_y, diameter, drill in plan['vias']:
        spot = (MM(pos_x), MM(pos_y))
        clear_along(board, net, board.GetLayerID('F.Cu'), MM(diameter), spot, spot)
        clear_along(board, net, board.GetLayerID('In2.Cu'), MM(diameter), spot, spot)
        clear_along(board, net, board.GetLayerID('B.Cu'), MM(diameter), spot, spot)
        via = pcbnew.PCB_VIA(board)
        via.SetPosition(pcbnew.VECTOR2I(*spot))
        via.SetViaType(pcbnew.VIATYPE_THROUGH)
        via.SetWidth(MM(diameter))
        via.SetDrill(MM(drill))
        via.SetNet(net_of(board, net))
        board.Add(via)
        KEEP.append(via)


def main():
    source, target = sys.argv[1:3]
    parts, nets = pcbnetlist.load_netlist()
    plan = load_placement()
    spots = plan['parts']
    board = pcbnew.LoadBoard(source)
    pin_net = {(ref, pin): name for name, nodes in nets.items() for ref, pin in nodes}

    remove_retired(board, parts)
    swapped = swap_footprints(board, parts, spots)
    present = {footprint.GetReference() for footprint in board.GetFootprints()}
    for ref in sorted(set(parts) - present):
        add_part(board, ref, parts[ref], spots.get(ref, [125.0, 50.0, 0, False]))
    for ref, spot in spots.items():
        place(board.FindFootprintByReference(ref), *spot)

    for zone in list(board.Zones()):
        name = zone.GetNetname()
        box = plan['removed_plus3v3_box']
        first = zone.Outline().CVertex(0)
        old_tab_pour = name == '+3V3' and zone.GetLayer() == pcbnew.F_Cu and inside(first, box)
        if name in plan['removed_zones'] or old_tab_pour:
            drop(board, zone)

    for item in list(board.GetTracks()):
        name = item.GetNetname()
        name = RENAMES.get(name, name)
        if name not in nets:
            drop(board, item)
        else:
            item.SetNet(net_of(board, name))
    for spec in plan['rips']:
        rip(board, spec)

    no_net = board.FindNet(0)
    for footprint in board.GetFootprints():
        ref = footprint.GetReference()
        if ref not in parts:
            continue
        footprint.SetValue(parts[ref]['value'])
        for pad in footprint.Pads():
            name = pin_net.get((ref, pad.GetNumber()))
            pad.SetNet(net_of(board, name) if name else no_net)

    add_copper(board, plan)
    cut = set()
    for ref in sorted(set(spots) | set(swapped) | (set(parts) - present)):
        cut |= clear_copper_under(board, board.FindFootprintByReference(ref))
    print('cut by moved parts:', sorted(cut))
    pcbnew.ZONE_FILLER(board).Fill(board.Zones())
    board.Save(target)


if __name__ == '__main__':
    main()

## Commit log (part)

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2026-02-21 Adding on durration to telemetry
2026-02-21 telemetry update
2026-02-21 dashboard
2026-02-21 Telemetry
2026-02-21 serial commands
2026-02-21 State machine
2026-02-22 Adding ambient temperature sensor and rms logic
2026-02-22 Lots of changes
2026-02-23 Telemetry FrameBuilder class, ACS712 non blocking updates, misc
2026-02-23 Renaming the ACS712 lib
2026-02-23 Adding JSON output for web, adding readme
2026-02-23 Adding docs
2026-02-23 These are not the droids you are looking for.
2026-02-23 Tests
2026-02-24 Add ContinuousZMCT103C as git submodule
2026-02-24 Removing continuous ac712
2026-02-24 Shutdown logic
2026-02-25 accelerometer
2026-02-25 Creating a serial studio dashboard generator, creating the tcp socket for it
2026-02-25 misc
2026-02-26 Damn, this was a lot
2026-02-26 Renamed the device dashboard submodule
2026-02-26 Adding the base module for the cooling pump
2026-02-26 weefee
2026-02-26 Averaging the delta-temp. Adding a hostname.
2026-02-26 dash
2026-02-27 cooling stuff
2026-02-27 Dependencies
2026-02-27 stuff
2026-02-27 Removing the index dependency for the dashboard
2026-02-28 adding some i2c changes, and misc
2026-02-28 Integration hell
2026-02-28 rm irrelevant stuff
2026-02-28 Having telemetry and dashboard init first
2026-03-01 FSM overhall
2026-03-01 Fixing fsm
2026-03-01 Mock data stuff
2026-03-01 submodule
2026-03-01 Finite state machine updates
2026-03-02 More mocks, and other updates
2026-03-02 Moving DAC, Waveform and RMS modules into a single Amplifier module. And other stuff
2026-03-02 Adding new amplifier module, and a ton of other changes
2026-03-02 getting it working
2026-03-02 so irritated
2026-03-03 working, and cleaning it up
2026-03-03 Disabling the gyroscope, renaming variables
2026-03-03 Working on FSM
2026-03-04 Adding the tracking monitor poc code. Untested
2026-03-04 adding logging to sd card
2026-03-05 fixing tracking
2026-03-06 Many a changes
2026-03-06 OTA Updates ftw
2026-03-06 Switching the DAC, and removing the ADC
2026-03-06 No more waiting on serial
2026-03-06 millis
2026-03-06 espnow
2026-03-07 Fixing fsm, moving dependency check to fsm start state prechecks
2026-03-08 Switching out some of the modules; fixing mock;
2026-03-08 WIP - Broken
2026-03-08 Current code with mock and dependency check refactor
2026-03-09 Fault handling refactor
2026-03-09 More refactoring, cleaning up
2026-03-09 Dashboard 2.0
2026-03-09 blah
2026-03-09 Dashboard is kinda workin
2026-03-10 Getting relay working
2026-03-11 Fixing a few things.
2026-03-11 Fixing the fam/pump rpm readings
2026-03-11 Adding logs to http output
2026-03-11 Fixing the serial bug. No thanks to AI, jeez
2026-03-11 works great
2026-03-11 Getting everything to use celcius, no kelvin
2026-03-12 Workin out the bugs; switched the relay module
2026-03-12 New telemetry format
2026-03-12 Implementing telemetry updates and misc formatting changes
2026-03-12 simplifying jsx components
2026-03-13 Pump speed fix
2026-03-13 Implementing custom RTD methods
2026-03-13 adding submodule
2026-03-13 Updating SerialStudio dash
2026-03-13 not working yet
2026-03-13 Fixing the faults in dashboad, and a fsm state loop
2026-03-13 Fixing cooling
2026-03-14 not totally working yet.
2026-03-15 Working
2026-03-15 Minor updates
2026-03-15 it wooorkss
2026-03-17 Updating dashboard, fixing a few things, changing the voltage based logic to fractions
2026-03-17 Adding reconnect wrapper.
2026-03-18 Reconnect logic, and other fixes
2026-03-18 telemetry updates
2026-03-20 Updating UI styles
2026-03-20 Faster loading dashboard
2026-03-20 updating dashboard related stuff
2026-03-21 implementing different RTD sensor
2026-03-22 Clearing temp on startup.
2026-03-22 Fixing test
2026-04-07 switching to internal LSM6DSOX IMU feature for overstroke detection
2026-04-09 fixed the fans
2026-04-09 reorganizing modules
2026-04-29 Still some ACS issues
2026-06-08 misc changes
